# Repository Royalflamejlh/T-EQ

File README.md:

# T EQ Pedal

This project's goal is to just make a simple home made equalizer pedal for a standard guitar.

The project started work from schematic of the [Rock Bottom EQ](https://www.diyguitarpedals.com.au/shop/boms/Rock%20Bottom%20EQ.pdf) and adapted it into our own schematic.

## Current Status

As of right now the first prototype of the pedal has been tested and we found some pretty big grounding problems, along with instability in the power supply circuity.

## Editing

The project can be opened and edited in KiCad 8

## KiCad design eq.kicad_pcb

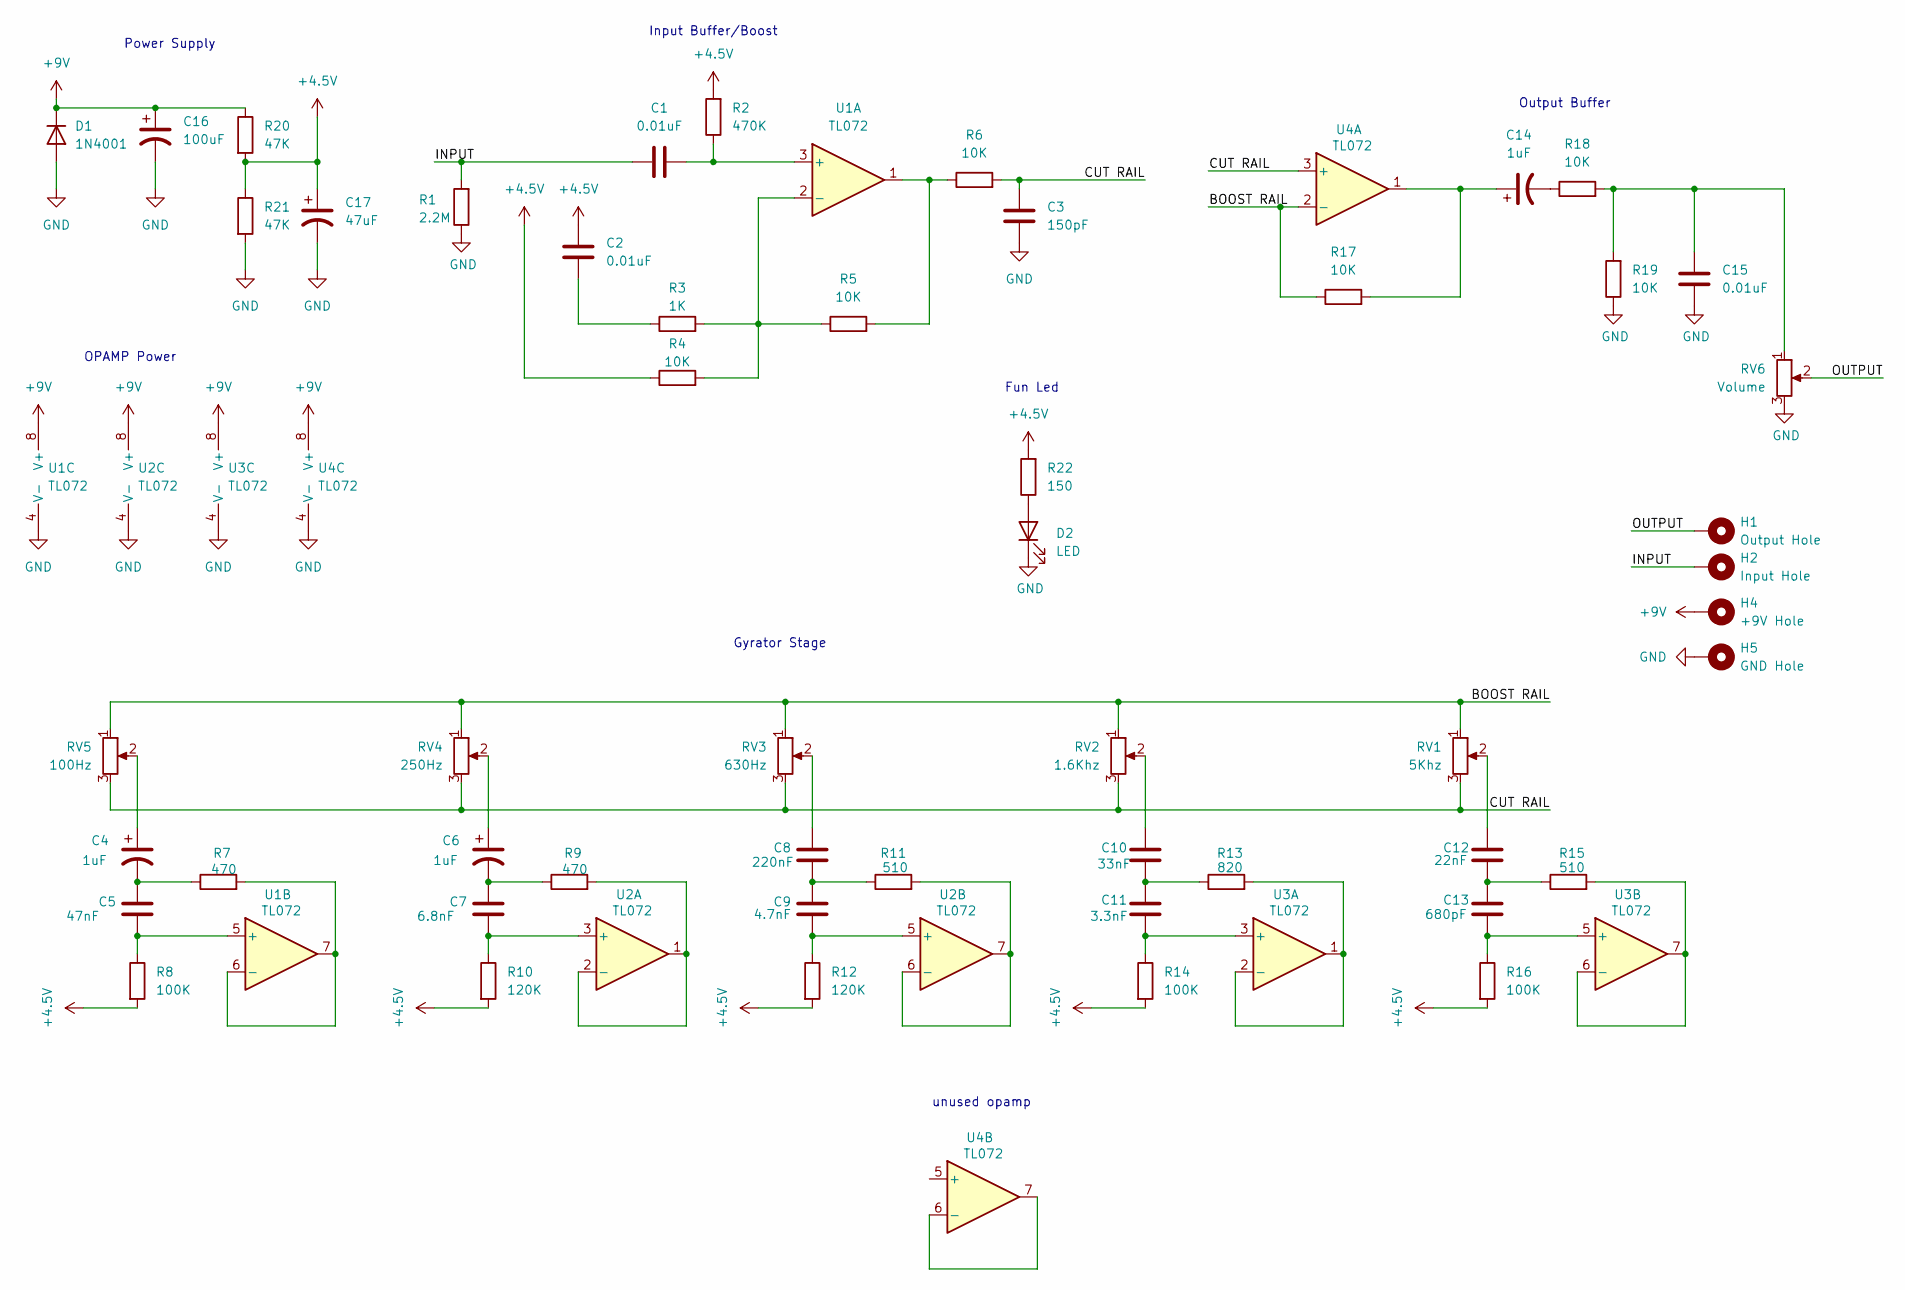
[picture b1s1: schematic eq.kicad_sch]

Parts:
C1, C2: 0.01uF; C_Rect_L7.2mm_W3.5mm_P5.00mm_FKS2_FKP2_MKS2_MKP2
C3: 150pF; C_Rect_L7.2mm_W5.5mm_P5.00mm_FKS2_FKP2_MKS2_MKP2
C4, C6, C14: 1uF; C_Radial_D4.0mm_H7.0mm_P1.50mm
C5: 47nF; C_Rect_L13.0mm_W6.0mm_P10.00mm_FKS3_FKP3_MKS4
C7: 6.8nF; C_Rect_L18.0mm_W8.0mm_P15.00mm_FKS3_FKP3
C8: 220nF; C_Rect_L9.0mm_W3.2mm_P7.50mm_MKT
C9: 4.7nF; C_Rect_L7.0mm_W2.5mm_P5.00mm
C10: 33nF; C_Rect_L18.0mm_W9.0mm_P15.00mm_FKS3_FKP3
C11: 3.3nF; C_Rect_L11.0mm_W6.4mm_P10.00mm_MKT
C12: 22nF; C_Rect_L13.0mm_W5.0mm_P10.00mm_FKS3_FKP3_MKS4
C13: 680pF; C_Disc_D16.0mm_W5.0mm_P10.00mm
C15: 0.01uF; C_Rect_L13.0mm_W5.0mm_P10.00mm_FKS3_FKP3_MKS4
C16: 100uF; CP_Radial_D8.0mm_P3.50mm
C17: 47uF; CP_Radial_D5.0mm_P2.00mm
D1: 1N4001; D_5W_P5.08mm_Vertical_AnodeUp
D2: LED; LED_D4.0mm
H1: Output Hole; MountingHole_5.5mm_Pad
H2: Input Hole; MountingHole_5.5mm_Pad
H4: +9V Hole; MountingHole_5.5mm_Pad
H5: GND Hole; MountingHole_5.5mm_Pad
R1: 2.2M; R_Axial_DIN0207_L6.3mm_D2.5mm_P7.62mm_Horizontal
R2: 470K; R_Axial_DIN0207_L6.3mm_D2.5mm_P7.62mm_Horizontal
R3: 1K; R_Axial_DIN0309_L9.0mm_D3.2mm_P12.70mm_Horizontal
R4, R5, R6, R17, R18, R19: 10K; R_Axial_DIN0207_L6.3mm_D2.5mm_P7.62mm_Horizontal
R7, R9: 470; R_Axial_DIN0207_L6.3mm_D2.5mm_P7.62mm_Horizontal
R8, R14, R16: 100K; R_Axial_DIN0207_L6.3mm_D2.5mm_P7.62mm_Horizontal
R10, R12: 120K; R_Axial_DIN0207_L6.3mm_D2.5mm_P7.62mm_Horizontal
R11, R15: 510; R_Axial_DIN0207_L6.3mm_D2.5mm_P7.62mm_Horizontal
R13: 820; R_Axial_DIN0207_L6.3mm_D2.5mm_P7.62mm_Horizontal
R20, R21: 47K; R_Axial_DIN0207_L6.3mm_D2.5mm_P7.62mm_Horizontal
R22: 150; R_Axial_DIN0207_L6.3mm_D2.5mm_P7.62mm_Horizontal
RV1: 5Khz; Potentiometer_Omeg_PC16BU_Vertical
RV2: 1.6Khz; Potentiometer_Omeg_PC16BU_Vertical
RV3: 630Hz; Potentiometer_Omeg_PC16BU_Vertical
RV4: 250Hz; Potentiometer_Omeg_PC16BU_Vertical
RV5: 100Hz; Potentiometer_Omeg_PC16BU_Vertical
RV6: Volume; Potentiometer_Omeg_PC16BU_Vertical
U1, U2, U3, U4: TL072; DIP794W45P254L959H508Q8

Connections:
+4.5V: C2.1, C17.1, R2.2, R4.1, R8.2, R10.2, R12.2, R14.2, R16.2, R20.2, R21.1, R22.2
+9V: C16.1, D1.1 (K), H4.1, R20.1, U1.8 (V+), U2.8 (V+), U3.8 (V+), U4.8 (V+)
/BOOST RAIL: R17.1, RV1.1, RV2.1, RV3.1, RV4.1, RV5.1, U4.2 (-); also elsewhere on the board
/CUT RAIL: C3.1, R6.2, RV1.3, RV2.3, RV3.3, RV4.3, RV5.3, U4.3 (+); also elsewhere on the board
/INPUT: C1.1, H2.1, R1.2
/OUTPUT: H1.1, RV6.2
GND: C3.2, C15.2, C16.2, C17.2, D1.2 (A), D2.1 (K), H5.1, R1.1, R19.1, R21.2, RV6.3, U1.4 (V-), U2.4 (V-), U3.4 (V-), U4.4 (V-)
unnamed: C2.2, R3.1
unnamed 8: C4.1, RV5.2; also elsewhere on the board
unnamed: C4.2, C5.1, R7.1
unnamed 10: C6.1, RV4.2; also elsewhere on the board
unnamed: C6.2, C7.1, R9.1
unnamed 12: C8.1, RV3.2; also elsewhere on the board
unnamed: C8.2, C9.1, R11.1
unnamed 14: C10.1, RV2.2; also elsewhere on the board
unnamed: C10.2, C11.1, R13.1
unnamed 16: C12.1, RV1.2; also elsewhere on the board
unnamed: C12.2, C13.1, R15.1
unnamed: C14.1, R17.2, U4.1
unnamed: C14.2, R18.1
unnamed: C15.1, R18.2, R19.2, RV6.1
unnamed: D2.2 (A), R22.1
unnamed: R5.2, R6.1, U1.1
unnamed: C1.2, R2.1, U1.3 (+)
unnamed: R3.2, R4.2, R5.1, U1.2 (-)
unnamed: C5.2, R8.1, U1.5 (+)
unnamed: R7.2, U1.6 (-), U1.7
unnamed: C7.2, R10.1, U2.3 (+)
unnamed: R9.2, U2.1, U2.2 (-)
unnamed: C9.2, R12.1, U2.5 (+)
unnamed: R11.2, U2.6 (-), U2.7
unnamed: C11.2, R14.1, U3.3 (+)
unnamed: R13.2, U3.1, U3.2 (-)
unnamed: C13.2, R16.1, U3.5 (+)
unnamed: R15.2, U3.6 (-), U3.7
unnamed: U4.6 (-), U4.7

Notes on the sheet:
Input Buffer/Boost
Gyrator Stage
Power Supply
Output Buffer
OPAMP Power
unused opamp
Fun Led

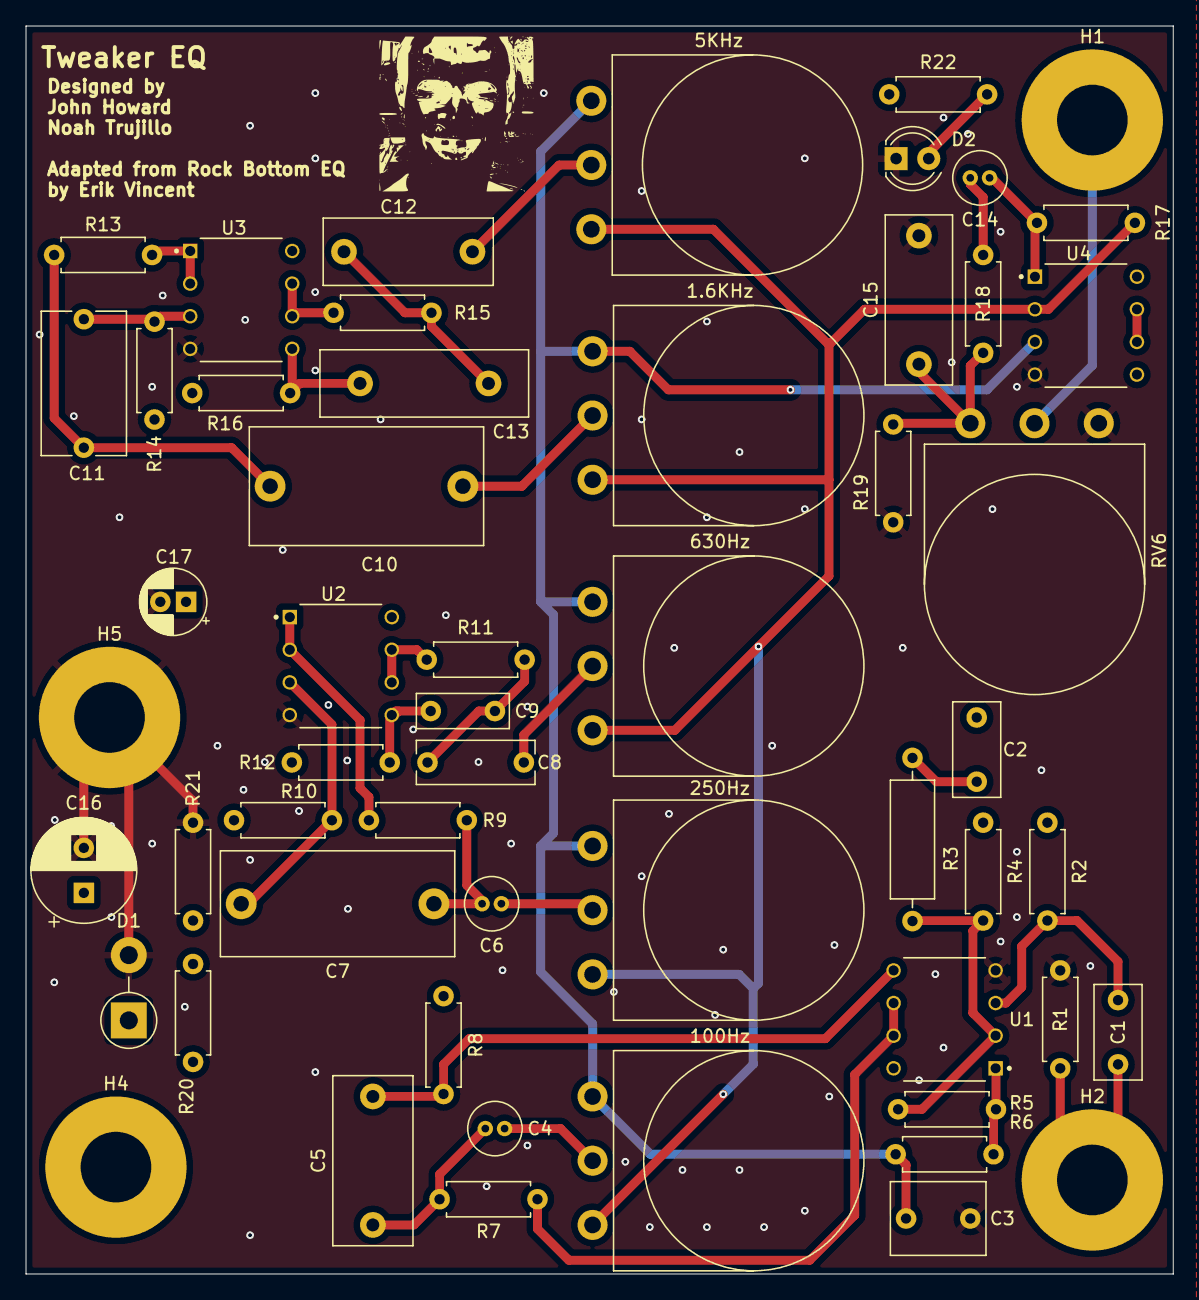
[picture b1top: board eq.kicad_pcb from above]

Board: 4 copper layers, 89.3 x 97.1 mm, 55 parts (0 on the bottom side), 36 nets.

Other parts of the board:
1.6KHz: 1.6Khz; Potentiometer_Omeg_PC16BU_Vertical
5KHz: 5Khz; Potentiometer_Omeg_PC16BU_Vertical
100Hz: 100Hz; Potentiometer_Omeg_PC16BU_Vertical
250Hz: 250Hz; Potentiometer_Omeg_PC16BU_Vertical
630Hz: 630Hz; Potentiometer_Omeg_PC16BU_Vertical

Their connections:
/BOOST RAIL: 1.6KHz.1, 5KHz.1, 100Hz.1, 250Hz.1, 630Hz.1; also elsewhere on the board
/CUT RAIL: 1.6KHz.3, 5KHz.3, 100Hz.3, 250Hz.3, 630Hz.3; also elsewhere on the board
unnamed 8: 100Hz.2; also elsewhere on the board
unnamed 10: 250Hz.2; also elsewhere on the board
unnamed 12: 630Hz.2; also elsewhere on the board
unnamed 14: 1.6KHz.2; also elsewhere on the board
unnamed 16: 5KHz.2; also elsewhere on the board

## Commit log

2024-08-02 Added todo list
